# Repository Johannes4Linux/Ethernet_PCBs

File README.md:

# PCBs for GNU/Linux & Ethernet Tutorials

This repositroy contains the KiCad Designs for the following PCBs:

- W7500 MAC Card: A PCB with the Wiznet W7500 chip which can be used as an SPI to Ethernet card. The PCB allows access to the MII over a pinheader and various Ethernet Transceiver Evaluation Boards can be connected to it.
- LAN8710A Ethernet Transceiver Card: PCB with the Microchip LAN8710A Ethernet Transceiver. The PCB can be connected to the *W7500 MAC Card* over the MII pinheader

## License

This documentation describes Open Hardware and is licensed under the CERN OHL S v2.

You may redistribute and modify this documentation under the terms of the CERN OHL S v2 ([http://ohwr.org/cernohl](http://ohwr.org/cernohl)). This documentation is distributed WITHOUT ANY EXPRESS OR IMPLIED WARRANTY, INCLUDING OF MERCHANTABILITY, SATISFACTORY QUALITY AND FITNESS FOR A PARTICULAR PURPOSE. Please see the CERN OHL S v2 for applicable conditions.

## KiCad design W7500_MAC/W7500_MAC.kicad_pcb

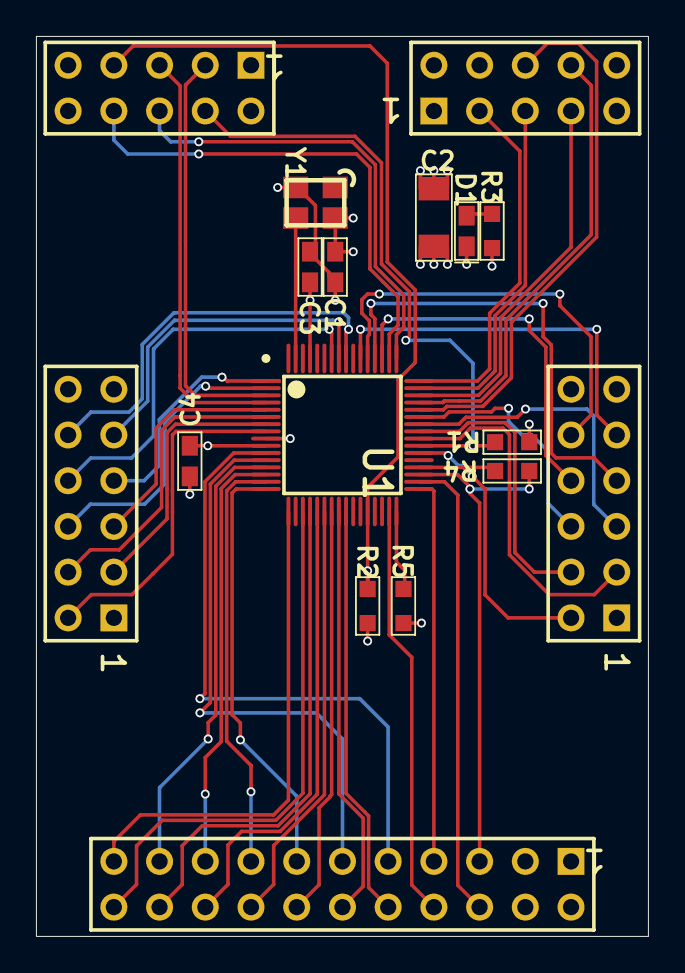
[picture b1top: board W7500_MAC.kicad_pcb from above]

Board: 4 copper layers, 34.0 x 50.0 mm, 17 parts (0 on the bottom side), 53 nets.

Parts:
C1, C3, C4: 100nF 0603; 0603_CAP
C2: 10uF 1206; 1206_CAP
D1: LED0; 0603_LED
P1, P4: Header 5X2; HDR2X5
P2, P3: Header 6X2; HDR2X6
P5: Header 11X2H; HDR2X11
R1, R2, R5: 4k7 0603; 0603
R3, R4: 330R 0603; 0603
U1: W7500; W7500_64pin
Y1: 8MHz 3225; XTAL_3225

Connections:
BOOT: P1.4, R1.2, U1.39
COL: P5.10, U1.25
CRS: P5.9, U1.11
CS: P4.8, U1.45
GND: C1.1, C2.1, C3.1, C4.1, D1.2, P1.9, P1.10, P2.11, P2.12, P3.11, P3.12, P4.4, P4.9, P5.3, P5.4, R1.1, R5.1, U1.9, Y1.2
IRQ: P4.6, U1.44
ISP_RXD: P1.5, U1.4
ISP_TXD: P1.3, U1.3
MDC: P5.6, U1.34
MDIO: P5.5, R4.1, U1.35
MISO: P4.5, U1.47
MOSI: P4.3, U1.48
NetD1_1: D1.1, R3.1
NetR4_2: R4.2, U1.36
NetU1_63: U1.63, Y1.3
PA_10: P2.2, U1.38
PA_11: P2.3, U1.40
PA_12: P2.4, U1.41
PA_13: P2.5, U1.42
PA_14: P2.6, U1.43
PC_00: P2.10, U1.53
PC_01: P2.9, U1.54
PC_03: P3.10, U1.56
PC_04: P3.9, U1.57
PC_05: P3.8, U1.58
PC_06: P2.8, U1.51
PC_07: P2.7, U1.52
PC_08: P3.7, U1.1
PC_09: P3.6, U1.2
PC_12: P3.5, U1.5
PC_13: P3.4, U1.6
PC_14: P3.3, U1.7
PC_15: P3.2, U1.8
PHY_IRQ: P5.8, U1.31
PHY_RST: P5.7, U1.33
RESET: P1.7, R2.1, U1.28
RXCLK: P5.21, U1.17
RXD0: P5.19, U1.13
RXD1: P5.17, U1.14
RXD2: P5.15, U1.15
RXD3: P5.13, U1.16
RXDV: P5.11, U1.12
SCLK: P4.7, U1.46
SWD_SWDCLK: P1.6, U1.49
SWD_SWDIO: P1.8, U1.50
TEST: R5.2, U1.32
TXCLK: P5.22, U1.19
TXD0: P5.20, U1.20
TXD1: P5.18, U1.21
TXD2: P5.16, U1.22
TXD3: P5.14, U1.23
TXEN: P5.12, U1.24
VCC_3V3: C1.2, C2.2, C3.2, C4.2, P1.1, P1.2, P2.1, P3.1, P4.1, P5.1, P5.2, R2.2, R3.2, U1.10, U1.61, Y1.4

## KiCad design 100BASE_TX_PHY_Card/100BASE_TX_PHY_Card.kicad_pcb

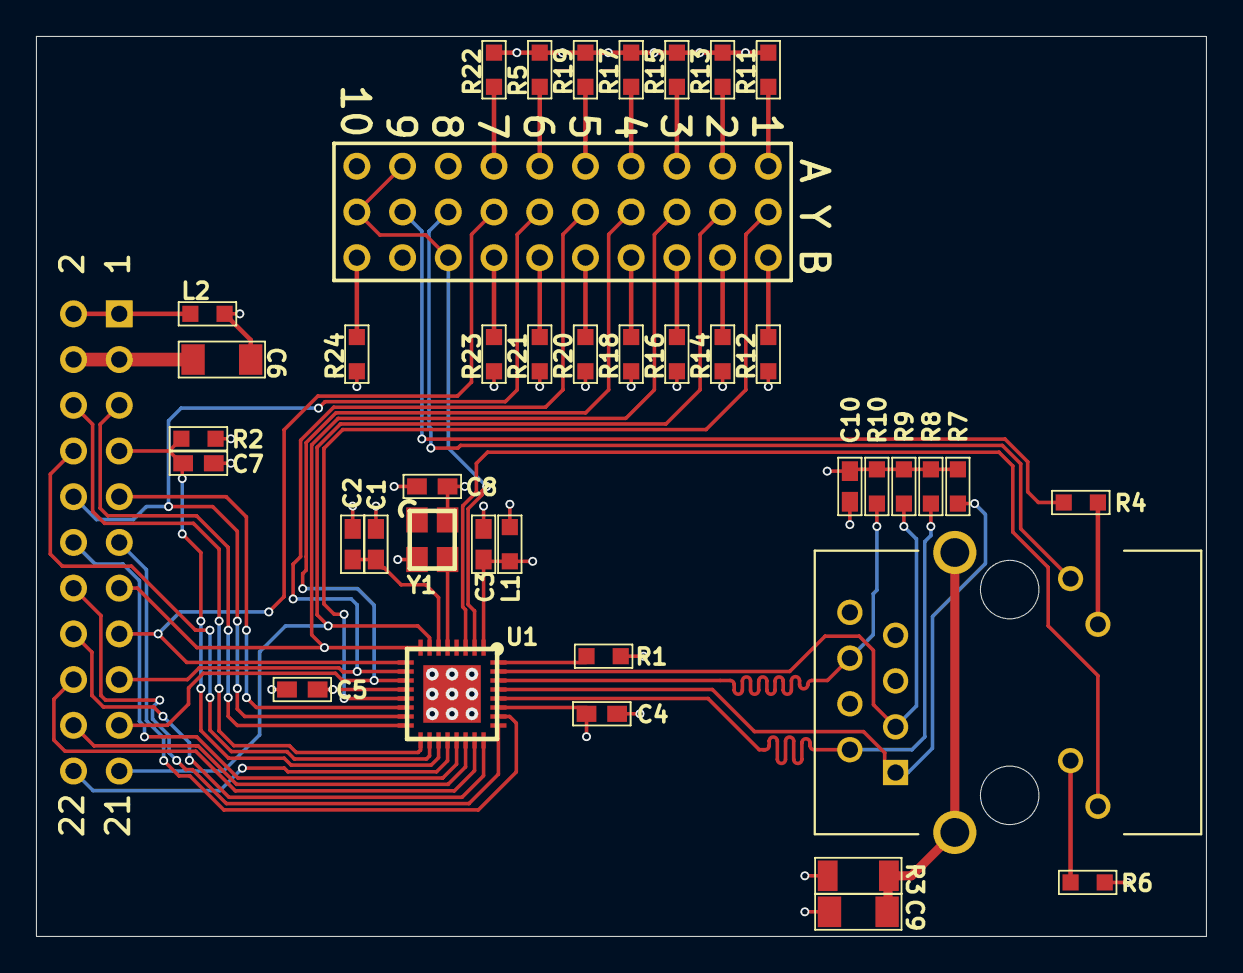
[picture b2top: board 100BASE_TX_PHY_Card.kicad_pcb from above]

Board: 4 copper layers, 65.0 x 50.0 mm, 41 parts (1 on the bottom side), 52 nets.

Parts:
C1: 470pF 0603; 0603_CAP
C2: 1uF 0603; 0603_CAP
C3, C4, C5, C7, C8: 100nF 0603; 0603_CAP
C6: 10uF 1206; 1206_CAP
C9: 10nF; 1206_CAP
C10: 15pF 0603; 0603_CAP
L1, L2: Ferrite bead 120R/100MHz; 0603_IND
P1: RJMG1BD3B8K1ANR
P2: SELECTOR 10WAY; SELECTOR_10WAY
P3: Header 11X2H; HDR2X11H
R1: 12k1 0603; 0603
R2: 100k 0603; 0603
R3: 1M 1206; 1206
R4, R6: 330R 0603; 0603
R5, R11, R12, R13, R14, R15, R16, R17, R18, R19, R20, R21, R22, R23, R24: 10k 0603; 0603
R7, R8, R9, R10: 49R9 0603; 0603
U1: LAN8710A
Y1: 25MHz 3225; XTAL_3225

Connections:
/MODE0: P2.11, P3.19, U1.11
/MODE1: P2.14, P3.17, U1.10
/MODE2: P2.17, P3.10, U1.15
/PHYAD0: P2.2, U1.13
/PHYAD1: P2.5, P3.21, U1.7
/PHYAD2: P2.8, P3.13, U1.8
/RMIISEL: P2.20, P3.15, U1.9
CRS: P3.9, U1.14
GND: C1.1, C2.1, C3.1, C4.1, C5.1, C6.1, C7.1, C8.1, C9.1, C10.1, P1.8, P2.27, P3.3, P3.4, R1.2, R3.2, R6.2, R12.1, R14.1, R16.1, R18.1, R20.1, R21.1, R23.1, R24.1, U1.0, Y1.2
LED1: P1.L4, U1.3
LED2: P2.24, P2.25, P2.29, U1.2
LED2+: P1.L1, P2.23
LED2-: P2.26, R4.2
MDC: P3.6, U1.17
MDIO: P3.5, U1.16
NetP1_L2: P1.L2, R4.1
NetP1_L3: P1.L3, R6.1
NetP2_1: P2.1, R11.2
NetP2_3: P2.3, R12.2
NetP2_4: P2.4, R13.2
NetP2_6: P2.6, R14.2
NetP2_7: P2.7, R15.2
NetP2_9: P2.9, R16.2
NetP2_10: P2.10, R17.2
NetP2_12: P2.12, R18.2
NetP2_13: P2.13, R19.2
NetP2_15: P2.15, R20.2
NetP2_16: P2.16, R5.2
NetP2_18: P2.18, R21.2
NetP2_19: P2.19, R22.2
NetP2_21: P2.21, R23.2
NetP2_30: P2.30, R24.2
NetR1_1: R1.1, U1.32
NetU1_5: U1.5, Y1.3
PHY_IRQ: P3.8, U1.18
PHY_RST: C7.2, P3.7, R2.1, U1.19
RXDV: P3.11, U1.26
RX_n: P1.6, R10.2, U1.30
RX_p: P1.3, R9.2, U1.31
SHIELD: C9.2, P1.S, R3.1
TXCLK: P3.22, U1.20
TXD0: P3.20, U1.22
TXD1: P3.18, U1.23
TXD2: P3.16, U1.24
TXD3: P3.14, U1.25
TXEN: P3.12, U1.21
TX_n: P1.2, R8.2, U1.28
TX_p: P1.1, R7.2, U1.29
VCC_3V3: L1.2, L2.2, P3.1, P3.2, R2.2, R5.1, R11.1, R13.1, R15.1, R17.1, R19.1, R22.1
VDDCR: C1.2, C2.2, U1.6
VDDIO: C5.2, C6.2, C8.2, L2.1, U1.12, Y1.4
VDD_A: C3.2, C4.2, C10.2, L1.1, P1.4, P1.5, P2.22, R7.1, R8.1, R9.1, R10.1, U1.1, U1.27

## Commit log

2024-09-01 Added README and license
2024-09-01 Upload first draft of W7500 MAC card design and LAN8710A card schematic
2024-09-27 LAN8710A PHY Card 4layer design
2024-09-28 Added missing Connectors schematic

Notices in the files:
100BASE_TX_PHY_Card/100BASE_TX_PHY_Card.kicad_pcb:
(c)2024 Uros Gaber, Johannes Roith
W7500_MAC/W7500_MAC.kicad_pcb:
(c)2024 Johannes Roith, Uros Gaber
